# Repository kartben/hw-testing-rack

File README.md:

# hw-testing-rack

**An all-printed, tilted test rack for development boards (12 in its default
4 × 3 layout) — every board in its own sliding drawer, power-switched,
current-metered and exposed over the network with USB/IP by a Zephyr-powered
ESP32-S3 in each bay.**

**[▶ Interactive 3D model](https://kartben.github.io/hw-testing-rack/)** · [Logic analyzer](https://kartben.github.io/hw-testing-rack/analyzer/) · [BOM](bom/README.md) ·
[Architecture](docs/architecture.md) · [Mechanics](docs/mechanical.md) · [Cabling](docs/cabling.md) ·
[Power](docs/power.md) · [Electronics](docs/electronics.md) · [Assembly](docs/assembly.md) ·
[Firmware](docs/firmware.md) · [Standalone bays](docs/standalone.md) · [CI](docs/ci.md)

## Highlights

* **Printed panel frame, no aluminium** — side walls ("ladders") shared by
  neighbouring bays, stacked row on row with snap hooks; trays slide into
  their grooves and click in; a taut X brace behind every bay keeps it square.
  Rows tilt 20° so every board, LED and label faces you, and the grid grows
  in both directions.
* **Drawers that stay connected** — each bay is a drawer sliding 140 mm along
  the slope; a drag chain hidden in the floor carries the cable, so you can
  pull a board out to probe it while it keeps running.
* **One plate for every board** — a honeycomb plate in each drawer; clip-in
  pegs (stops, cams, pins) hold any board on it, placed by a tool from a small
  board library (UNO, Nucleo-64/144, Pico, nRF DKs, FRDM, …): up to four small
  boards on one plate.
* **One ESP32-S3 per bay** — switches the board's 5 V (current-limited,
  default on), measures V/I (INA226), drives UART/RESET/BOOT lines, and
  exports the board's USB with Zephyr's USB/IP host service.  Plug a laptop
  into the bay's front port and the USB data path switches to it — the
  "classic" way still works, even with no firmware.
* **One USB-C charger** — a printed power box under the first column holds
  the hub: a USB PD 3.1 sink (20 or 28 V from one charger, no mains in the
  rack) and an eFuse per row; a 60 V-rated buck in every bay.  The same row
  cables carry a CAN bus for the rack controller ([can.md](docs/can.md)).
* **Cameras** — an optional Arducam Mega (SPI, 145° M12 lens) and white LEDs behind a diffuser hang from a bay's ceiling, driven by the bay's own node.
* **Everything is generated** from [`config/rack.yaml`](config/rack.yaml):
  OpenSCAD parts, KiCad schematics *and* PCBs (schematic-as-code, Freerouting),
  the BOM with LCSC part numbers, and the interactive viewer.

| | |
|---|---|
|  |  |
| Bay B3 pulled out, still connected: a DATA ×4 at the back serves two XIAOs and two Pico 2s | The DATA ×4 up close: a USB-C lead per board, Dupont jumpers wiring a UART between two of them ([real models](docs/boards-3d.md)) |
|  |  |
| Row B: the GIGA's LVGL screen in B2, between two DATA ×4 bays | Bay node — ESP32-S3 (8 MB PSRAM), 2 USB muxes, TPS26600 eFuse, INA226, CAN, 60 V buck |

Neutral technical renders: [the rack](docs/img/hero.jpg), [one bay exploded](docs/architecture.md),
[side view](docs/mechanical.md).

## Repository layout

```
config/rack.yaml          single source of truth (rows, bays, tilt, dimensions, population)
mechanical/               OpenSCAD: lib/, parts/, boards/boards.yaml, generated/ (from the config)
electronics/
  tools/                  schematic-as-code (eda.py), PCB builder (pcbgen.py), catalogue, LCSC resolver
  bay-node/               design.py + generated KiCad project, fab/, docs/
  power-hub/              design.py + generated KiCad project, fab/, docs/
  data-port-x6/           the drawer's DATA ×6, six USB-C, power only (the default): design.py + KiCad, fab/, docs/
  data-port-x4/           the DATA ×4 v2, four USB-C and the logic, for bays with wires: design.py + KiCad, fab/, docs/
  data-port/              the single-port board, retired from the rack, kept for the standalone Solo box
  camera-pod/             the camera pod's board (lead, camera header, 3.3 V, LEDs): design.py + KiCad, fab/, docs/
  lib/                    custom symbol(s), cached JLC basic passives
site/                     GitHub Pages: three.js viewer + BOM page (assets generated)
bom/                      full rack BOM (CSV + summary)
render/                   Blender scene + photoreal renders
tools/                    build.py (config/STL/web), kicad.sh, bom.py, jlc_mcp.py, notice/ (FreeCAD line art)
docs/                     design documentation
```

## Building

Prerequisites: Python ≥ 3.10 with `pyyaml numpy trimesh` (`pip install -r tools/requirements.txt`),
Docker (for KiCad 10, Freerouting and — if not installed locally — OpenSCAD).

```bash
python tools/build.py all                    # config → STLs → web viewer assets
tools/kicad.sh bay-node --route --fab        # schematic, PCB, autoroute, Gerbers/BOM/CPL, renders
tools/kicad.sh power-hub --route --fab
tools/kicad.sh data-port-x6 --fab            # fab outputs of the routed board, no re-route
tools/kicad.sh data-port-x4 --fab
tools/kicad.sh camera-pod --route --fab
python tools/bom.py                          # full rack BOM
python -m http.server -d site 8000           # open http://localhost:8000
```

Generated outputs (STLs, Gerbers, renders, PDFs, GLBs, the BOM) are committed with the change that alters
them, never for a date: `python tools/keep_unchanged.py` puts back every regenerated file whose content didn't
change (`tools/kicad.sh … --fab` runs it on its board).

For screenshots the viewer takes URL parameters: `?bay=B4&openbay=1&view=dut&hideui`
pulls bay B4's drawer out and frames its DUT cable (DATA port to board), with no UI.
`?bay=B2&view=camera&camlight=1&preview=B2` looks into a camera bay with its LEDs on and opens what
its camera sees (an Arducam Mega with a 145° lens: fisheye, noise, auto-exposure and JPEG, at 5 fps).

The viewer lights the rack like the photos: a real room (Poly Haven's "Small Empty Room 1", CC0, cut to
512 × 256 in `site/assets/env/`), AgX with Blender's "Medium High Contrast" look, PETG with its layer lines.
Its *High quality* box (on by default on a desktop GPU, off on phones and small GPUs, and dropped by itself
under 25 fps) adds ambient occlusion (GTAO), a glow on the status LEDs and the camera lights, 4× MSAA through
the post-processing and 4096² sun shadows; `?quality=high` or `?quality=low` forces one for screenshots.

Photoreal renders (Blender + Cycles) start from `render/assembly.glb`, baked
from the same scene as the viewer by `python tools/assembly_glb.py --hq` (`--hq`:
full-resolution part meshes instead of the viewer's lighter ones).  Either
render headless in Docker (`tools/render.sh hero`) or drive a Blender you
already have open — GPU and all — through the Blender MCP add-on's socket:

```bash
python tools/blender_live.py exec render/live_scene.py                    # (re)build the scene
python tools/blender_live.py exec render/live_render.py hero              # → docs/img/hero.jpg
python tools/blender_live.py exec render/live_render.py drawer:B3 docs/img/drawer.jpg

python tools/assembly_glb.py --hq --explode-bay B2 --out render/bay-exploded.glb   # one bay, layers apart
python tools/blender_live.py exec render/live_scene.py render/bay-exploded.glb
python tools/blender_live.py exec render/live_render.py exploded
```

The photo shots (`docs/img/photo-*.jpg`) use their own scene: a small office
lit through a window, PETG with 0.2 mm layer lines and
rounded edges, scanned oak and plaster (CC0 textures from Poly Haven), a laptop
showing a Zephyr shell, wired to bay B4 by a USB-C cable that hangs as a real
one would (a catenary), depth of field, bloom and a vignette, rendered at 2× and averaged down:

```bash
python tools/fetch_render_assets.py                     # CC0 textures + vendor board models → render/assets/
python tools/board_models.py                            # normalise the board models (docs/boards-3d.md)
python render/screen_terminal.py                        # the laptop's screen → render/assets/
node tools/lvgl_frame.mjs music 480 800                 # B2's GIGA display: one frame of the viewer's LVGL demo
                                                        # (the drawer fronts' status screens: assembly_glb.py draws them)
python tools/assembly_glb.py --hq --with-pc-cable --open-bays B3 --out render/assembly-photo.glb
python tools/blender_live.py exec render/live_photo.py build
python tools/blender_live.py exec render/live_photo.py shot desk          # desk, drawer, detail → docs/img/photo-*.jpg
```

Change the rack in `config/rack.yaml` (tilt, rows, columns, panel thickness,
which bays get cameras, which board sits where) and rebuild.

## Status

v0.2 — the printed panel frame replaces the aluminium frame, **not yet
built**.  Mechanics are printable and parametric, the power box included;
still to design: double-width bays (see [mechanical.md](docs/mechanical.md)).
Each drawer front carries the node's 1.9" touch display, waiting on the
module to check its fit before a test print.  Five PCBs (bay node, power hub,
DATA ×6, DATA ×4, camera pod) pass ERC and DRC, are routed and smoothed,
and went through a schematic review
([schematic-review-2026-10-25.md](docs/schematic-review-2026-10-25.md)) and a
datasheet audit.  **Their v1.0 went to fabrication on 2026-11-11** and is
frozen: a change to a board now takes a new revision
([electronics.md › Revisions at the fab](docs/electronics.md#revisions-at-the-fab)).
None is on the bench yet; what to check when they arrive:
[bring-up.md](docs/bring-up.md).  The node firmware:
[firmware.md](docs/firmware.md).
Board outlines marked `verified: false` in `boards.yaml` are approximate.

## License

Hardware (mechanical and electronics design files): **CERN-OHL-P-2.0**.
Software (tools, viewer, firmware): **Apache-2.0**.  See [LICENSE](LICENSE).

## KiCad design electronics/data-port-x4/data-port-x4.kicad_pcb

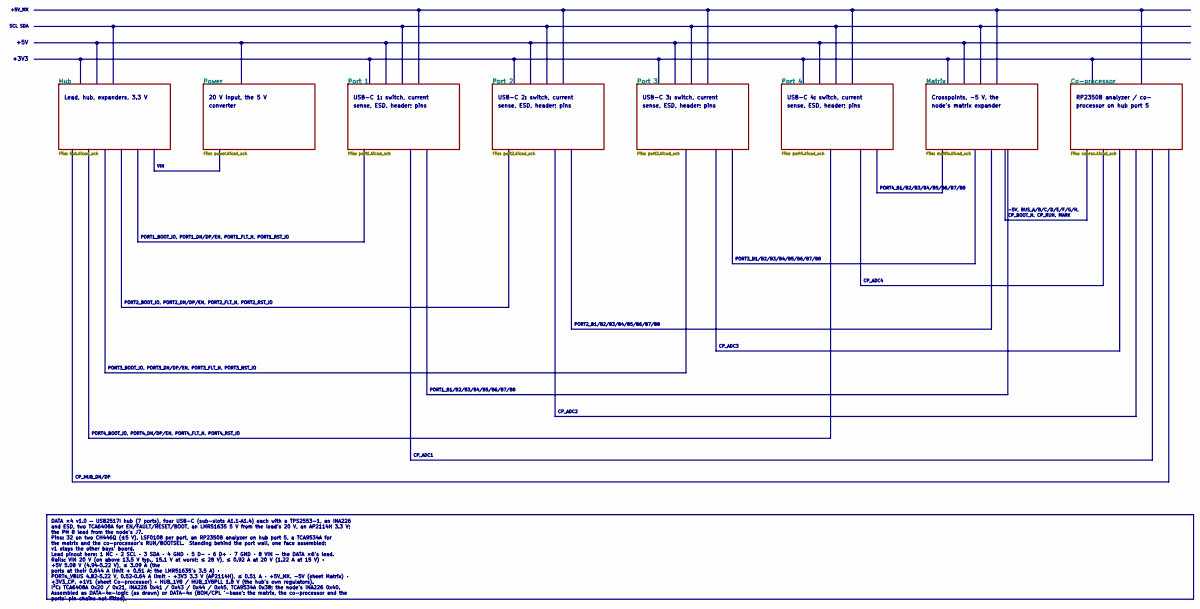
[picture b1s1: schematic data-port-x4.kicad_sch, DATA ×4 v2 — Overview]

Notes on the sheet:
Lead, hub, expanders, 3.3 V
20 V input, the 5 V
converter
USB-C 1: switch, current
sense, ESD, header; pins
USB-C 2: switch, current
USB-C 3: switch, current
USB-C 4: switch, current
Crosspoints, −5 V, the
node's matrix expander
RP2350B analyzer / co-
processor on hub port 5
+3V3
+5V
SCL SDA
+5V_MX
VIN
PORT4_B1/B2/B3/B4/B5/B6/B7/B8
-5V, BUS_A/B/C/D/E/F/G/H,
CP_BOOT_N, CP_RUN, MARK
PORT1_BOOT_IO, PORT1_DN/DP/EN, PORT1_FLT_N, PORT1_RST_IO
PORT3_B1/B2/B3/B4/B5/B6/B7/B8
CP_ADC4
PORT2_BOOT_IO, PORT2_DN/DP/EN, PORT2_FLT_N, PORT2_RST_IO
PORT2_B1/B2/B3/B4/B5/B6/B7/B8
CP_ADC3
PORT3_BOOT_IO, PORT3_DN/DP/EN, PORT3_FLT_N, PORT3_RST_IO
PORT1_B1/B2/B3/B4/B5/B6/B7/B8
CP_ADC2
PORT4_BOOT_IO, PORT4_DN/DP/EN, PORT4_FLT_N, PORT4_RST_IO
CP_ADC1
CP_HUB_DN/DP
DATA ×4 v1.0 — USB2517I hub (7 ports), four USB-C (sub-slots A1.1–A1.4) each with a TPS2553-1, an INA226 and ESD, two TCA6408A for EN/FAULT/RESET/BOOT, an LMR51635 5 V from the lead's 20 V, an AP2114H 3.3 V; the PH 8 lead from the node's J7. Pins: 32 on two CH446Q (±5 V), LSF0108 per port, an RP235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

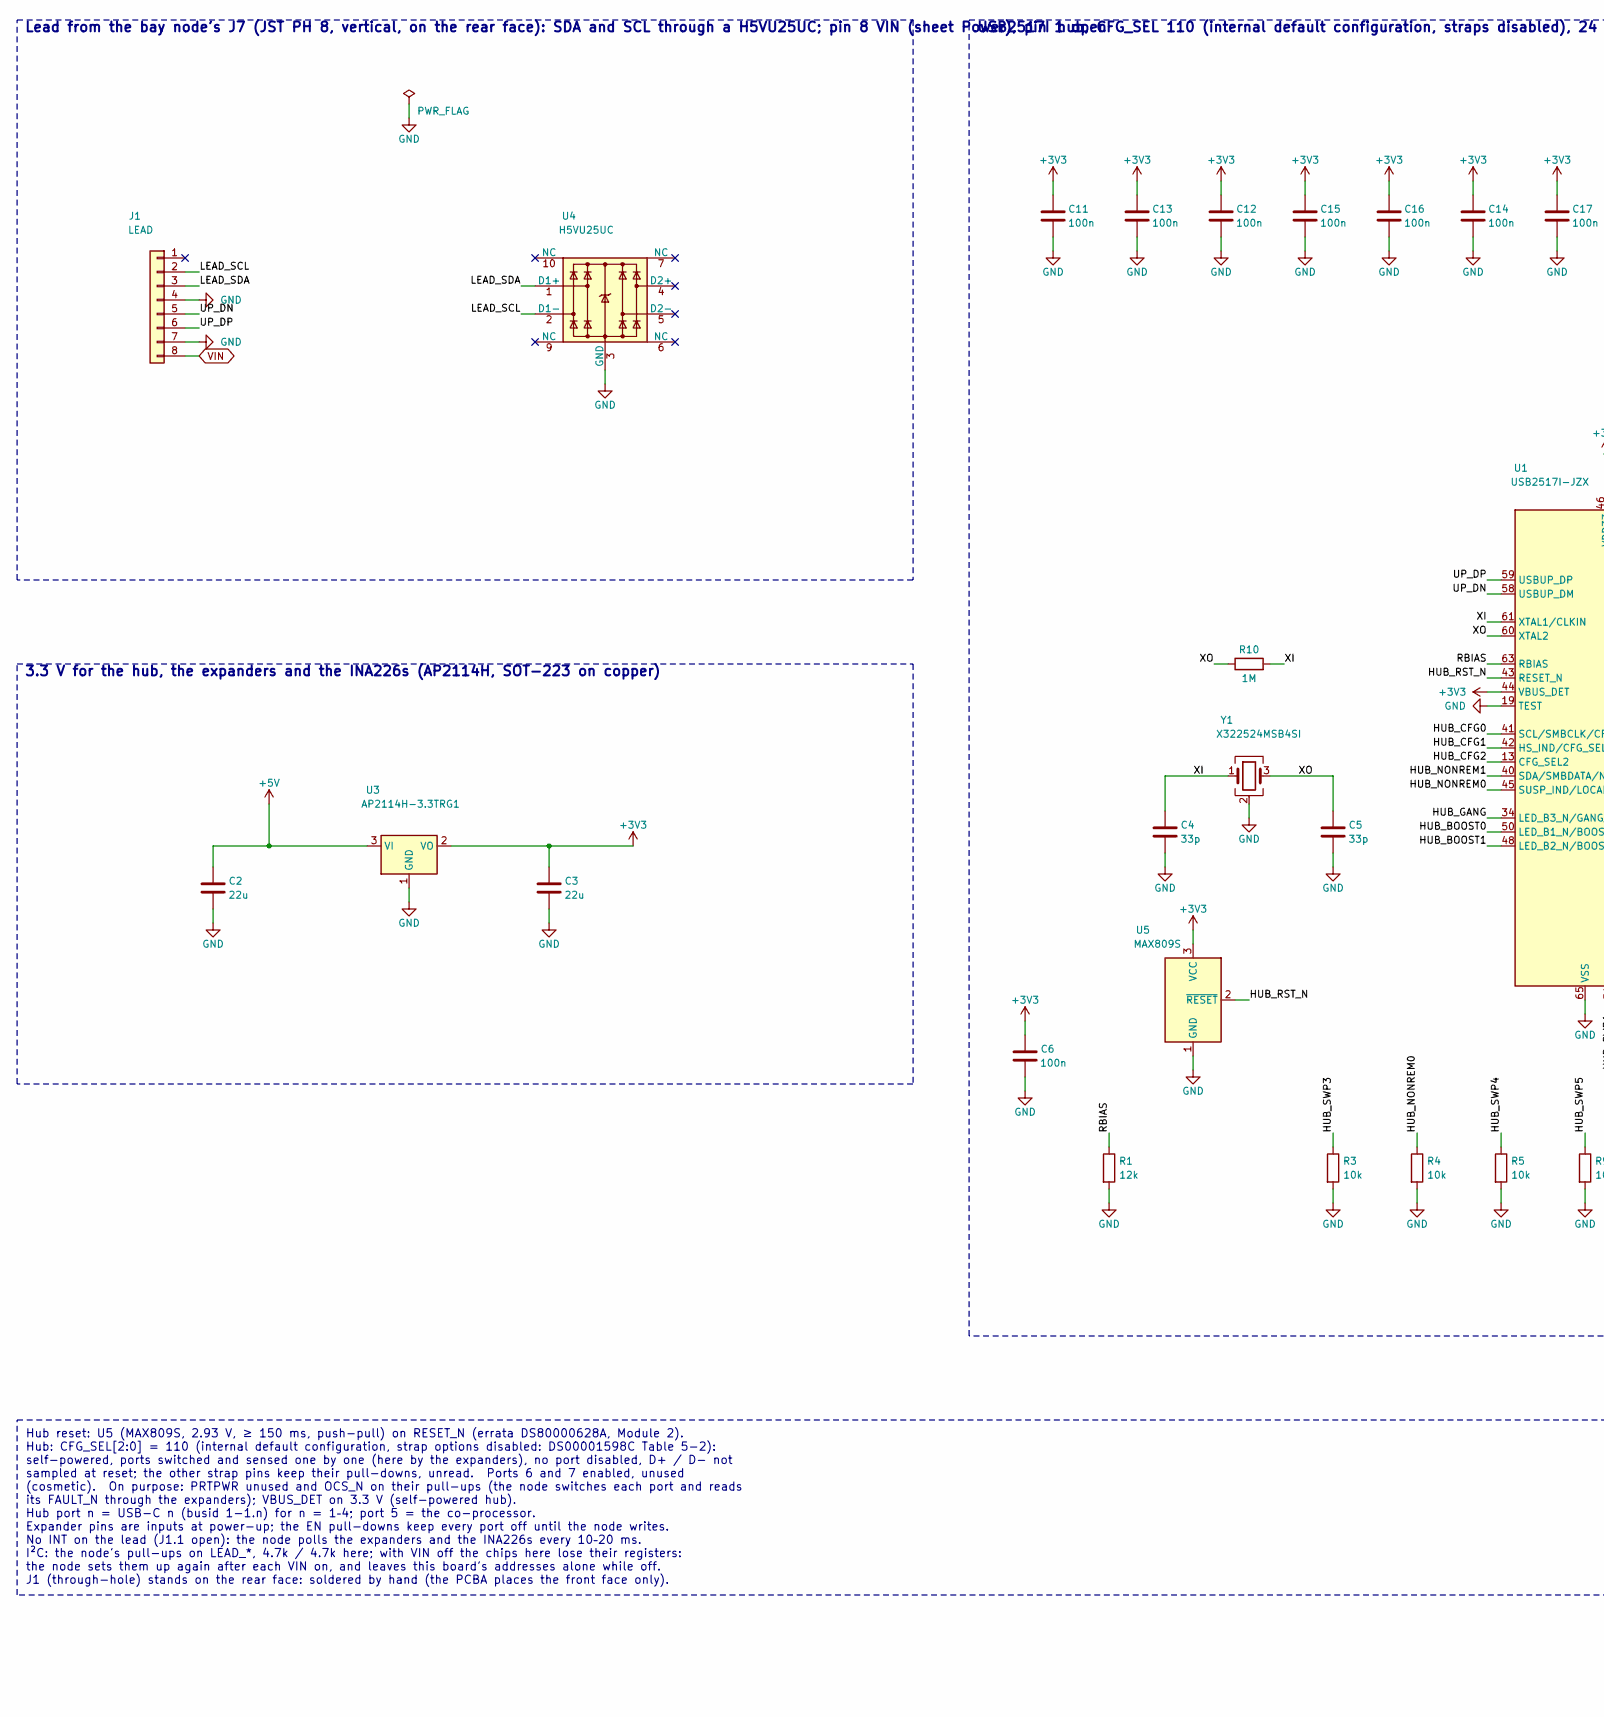
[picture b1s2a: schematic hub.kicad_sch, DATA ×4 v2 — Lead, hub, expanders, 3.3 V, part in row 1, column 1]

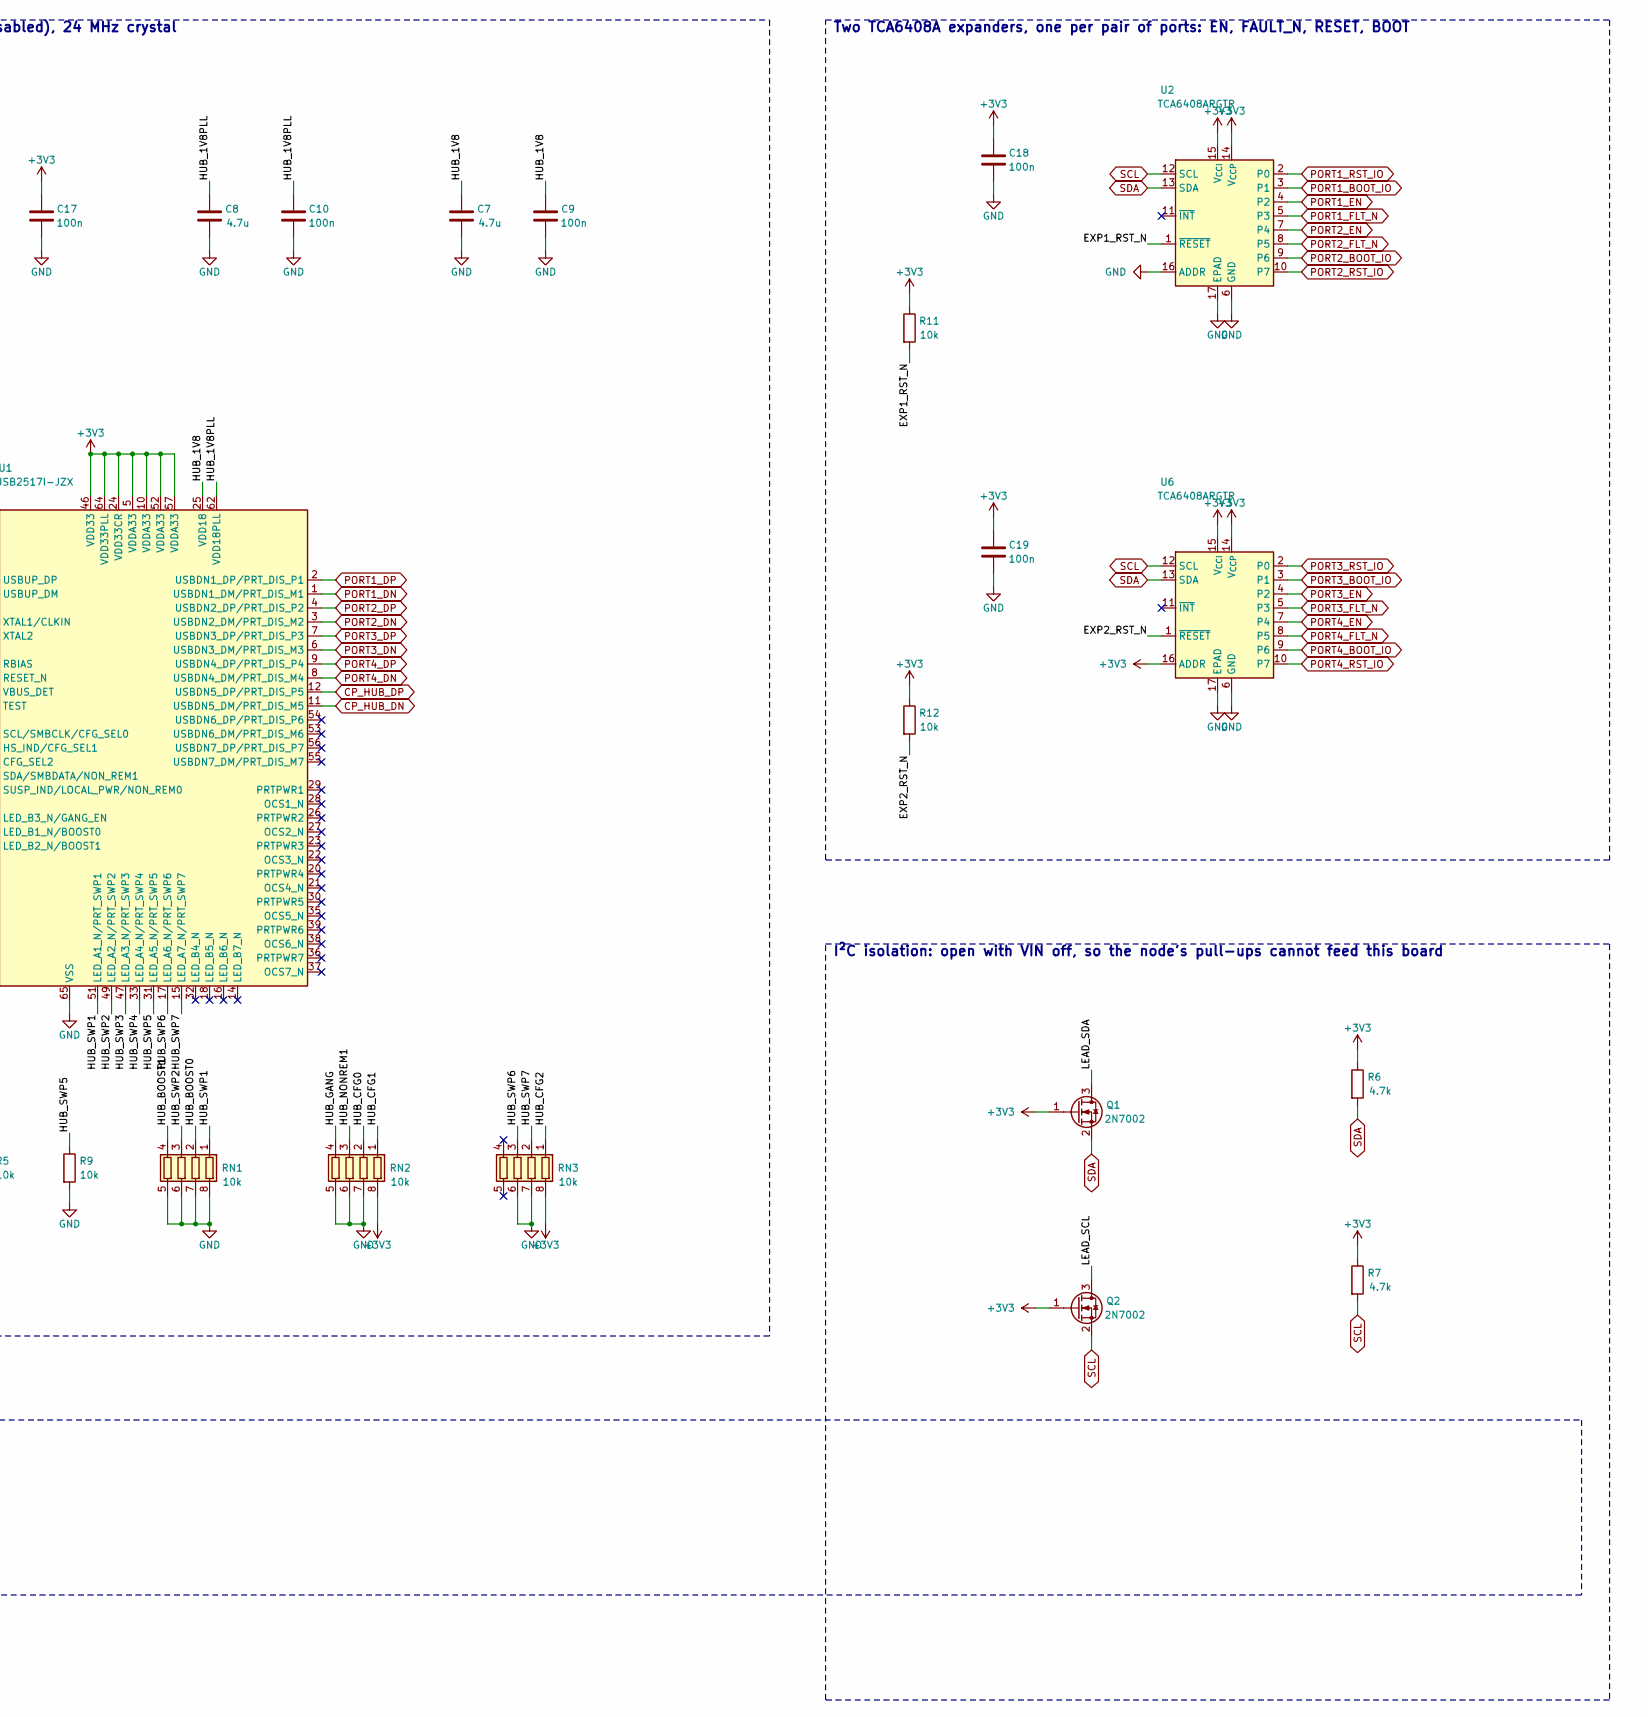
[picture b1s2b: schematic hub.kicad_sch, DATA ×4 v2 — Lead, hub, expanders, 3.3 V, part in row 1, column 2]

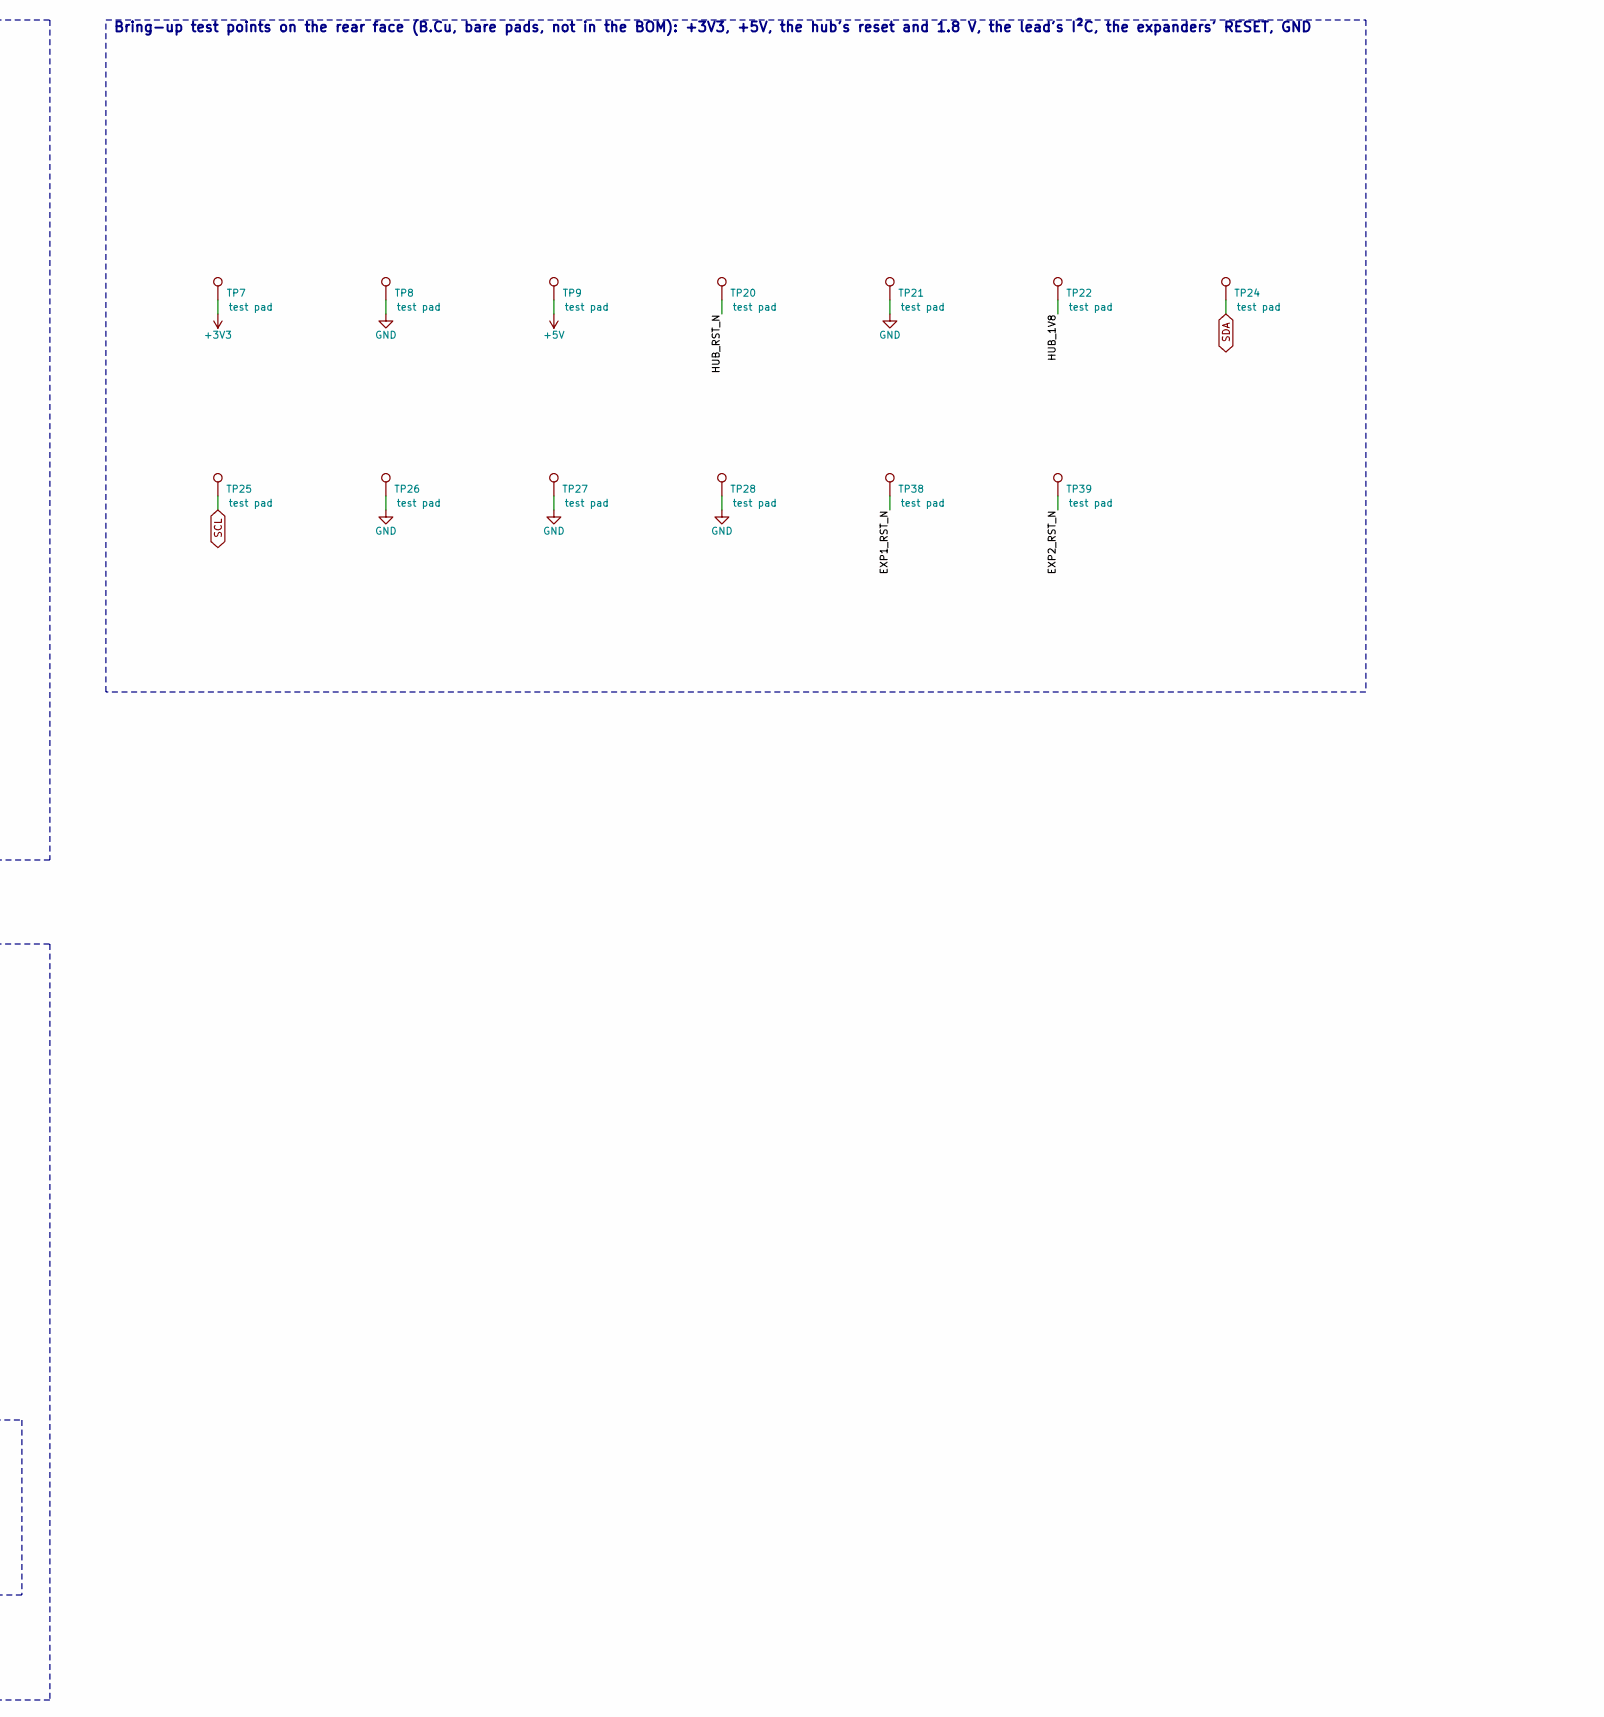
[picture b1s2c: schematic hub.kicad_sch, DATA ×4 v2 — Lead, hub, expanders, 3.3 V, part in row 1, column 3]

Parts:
C2, C3: 22u; C_0805_2012Metric; MPN CL21A226MAQNNNE; LCSC C45783
C4, C5: 33p; C_0402_1005Metric; MPN 0402CG330J500NT; LCSC C1562
C6, C9, C10, C11, C12, C13, C14, C15, C16, C17, C18, C19: 100n; C_0402_1005Metric; MPN CL05B104KO5NNNC; LCSC C1525
C7, C8: 4.7u; C_0402_1005Metric; MPN CL05A475MP5NRNC; LCSC C23733
J1: LEAD; JST_PH_B8B-PH-K_1x08_P2.00mm_Vertical; MPN B8B-PH-K-S(LF)(SN); LCSC C157974
Q1, Q2: 2N7002; SOT-23; MPN 2N7002; LCSC C8545
R1: 12k; R_0402_1005Metric; MPN 0402WGF1202TCE; LCSC C25752
R3, R4, R5, R9, R11, R12: 10k; R_0402_1005Metric; MPN 0402WGF1002TCE; LCSC C25744
R6, R7: 4.7k; R_0402_1005Metric; MPN 0402WGF4701TCE; LCSC C25900
R10: 1M; R_0402_1005Metric; MPN 0402WGF1004TCE; LCSC C26083
RN1, RN2, RN3: 10k; R_Array_Convex_4x0402; MPN 4D02WGJ0103TCE; LCSC C25725
TP7, TP8, TP9, TP21, TP22, TP26, TP27, TP28: test pad; TestPoint_Pad_D1.5mm; MPN test pad
TP20, TP24, TP25, TP38, TP39: test pad; TestPoint_Pad_D1.0mm; MPN test pad
U1: USB2517I-JZX; QFN-64-1EP_9x9mm_P0.5mm_EP4.7x4.7mm_Paste4x4; MPN USB2517I-JZX; LCSC C478081
U2, U6: TCA6408ARGTR; VQFN-16-1EP_3x3mm_P0.5mm_EP1.45x1.45mm; MPN TCA6408ARGTR; LCSC C181499
U3: AP2114H-3.3TRG1; SOT-223-3_TabPin2; MPN AP2114H-3.3TRG1; LCSC C150716
U4: H5VU25UC; DFN2510-10L_2.5x1.0mm_P0.5mm; MPN H5VU25UC; LCSC C20615800
U5: MAX809S; SOT-23; MPN MAX809S; LCSC C347371
Y1: X322524MSB4SI; Crystal_SMD_3225-4Pin_3.2x2.5mm; MPN X322524MSB4SI; LCSC C15643

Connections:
+3V3: C3.1, C6.1, C11.1, C12.1, C13.1, C14.1, C15.1, C16.1, C17.1, C18.1, C19.1, Q1.1 (G), Q2.1 (G), R6.1, R7.1, R11.1, R12.1, RN2.8 (R1.2), RN3.8 (R1.2), TP7.1, U1.5 (VDDA33), U1.10 (VDDA33), U1.24 (VDD33CR), U1.44 (VBUS_DET), U1.46 (VDD33), U1.52 (VDDA33), U1.57 (VDDA33), U1.64 (VDD33PLL), U2.14 (V_{CCP}), U2.15 (V_{CCI}), U3.2 (VO), U5.3 (VCC), U6.14 (V_{CCP}), U6.15 (V_{CCI}), U6.16 (ADDR); also elsewhere on the board
+5V: C2.1, TP9.1, U3.3 (VI); also elsewhere on the board
/Hub/EXP1_RST_N: R11.2, TP38.1, U2.1 (~RESET)
/Hub/EXP2_RST_N: R12.2, TP39.1, U6.1 (~RESET)
/Hub/HUB_1V8: C7.1, C9.1, TP22.1, U1.25 (VDD18)
/Hub/HUB_1V8PLL: C8.1, C10.1, U1.62 (VDD18PLL)
/Hub/HUB_BOOST0: RN1.2 (R2.1), U1.50 (LED_B1_N/BOOST0)
/Hub/HUB_BOOST1: RN1.4 (R4.1), U1.48 (LED_B2_N/BOOST1)
/Hub/HUB_CFG0: RN2.2 (R2.1), U1.41 (SCL/SMBCLK/CFG_SEL0)
/Hub/HUB_CFG1: RN2.1 (R1.1), U1.42 (HS_IND/CFG_SEL1)
/Hub/HUB_CFG2: RN3.1 (R1.1), U1.13 (CFG_SEL2)
/Hub/HUB_GANG: RN2.4 (R4.1), U1.34 (LED_B3_N/GANG_EN)
/Hub/HUB_NONREM0: R4.1, U1.45 (SUSP_IND/LOCAL_PWR/NON_REM0)
/Hub/HUB_NONREM1: RN2.3 (R3.1), U1.40 (SDA/SMBDATA/NON_REM1)
/Hub/HUB_RST_N: TP20.1, U1.43 (RESET_N), U5.2 (~RESET)
/Hub/HUB_SWP1: RN1.1 (R1.1), U1.51 (LED_A1_N/PRT_SWP1)
/Hub/HUB_SWP2: RN1.3 (R3.1), U1.49 (LED_A2_N/PRT_SWP2)
/Hub/HUB_SWP3: R3.1, U1.47 (LED_A3_N/PRT_SWP3)
/Hub/HUB_SWP4: R5.1, U1.33 (LED_A4_N/PRT_SWP4)
/Hub/HUB_SWP5: R9.1, U1.31 (LED_A5_N/PRT_SWP5)
/Hub/HUB_SWP6: RN3.3 (R3.1), U1.17 (LED_A6_N/PRT_SWP6)
/Hub/HUB_SWP7: RN3.2 (R2.1), U1.15 (LED_A7_N/PRT_SWP7)
/Hub/LEAD_SCL: J1.2, Q2.3 (D), U4.2 (D1-)
/Hub/LEAD_SDA: J1.3, Q1.3 (D), U4.1 (D1+)
/Hub/RBIAS: R1.1, U1.63 (RBIAS)
/Hub/UP_DN: J1.5, U1.58 (USBUP_DM)
/Hub/UP_DP: J1.6, U1.59 (USBUP_DP)
/Hub/XI: C4.1, R10.2, U1.61 (XTAL1/CLKIN), Y1.1
/Hub/XO: C5.1, R10.1, U1.60 (XTAL2), Y1.3
CP_HUB_DN: U1.11 (USBDN5_DM/PRT_DIS_M5); also elsewhere on the board
CP_HUB_DP: U1.12 (USBDN5_DP/PRT_DIS_P5); also elsewhere on the board
GND: C2.2, C3.2, C4.2, C5.2, C6.2, C7.2, C8.2, C9.2, C10.2, C11.2, C12.2, C13.2, C14.2, C15.2, C16.2, C17.2, C18.2, C19.2, J1.4, J1.7, R1.2, R3.2, R4.2, R5.2, R9.2, RN1.5 (R4.2), RN1.6 (R3.2), RN1.7 (R2.2), RN1.8 (R1.2), RN2.5 (R4.2), RN2.6 (R3.2), RN2.7 (R2.2), RN3.6 (R3.2), RN3.7 (R2.2), TP8.1, TP21.1, TP26.1, TP27.1, TP28.1, U1.19 (TEST), U1.65 (VSS), U2.6 (GND), U2.16 (ADDR), U2.17 (EPAD), U3.1 (GND), U4.3 (GND), U4.8 (GND), U5.1 (GND), U6.6 (GND), U6.17 (EPAD), Y1.2 (G), Y1.4 (G); also elsewhere on the board
PORT1_BOOT_IO: U2.3 (P1); also elsewhere on the board
PORT1_DN: U1.1 (USBDN1_DM/PRT_DIS_M1); also elsewhere on the board
PORT1_DP: U1.2 (USBDN1_DP/PRT_DIS_P1); also elsewhere on the board
PORT1_EN: U2.4 (P2); also elsewhere on the board
PORT1_FLT_N: U2.5 (P3); also elsewhere on the board
PORT1_RST_IO: U2.2 (P0); also elsewhere on the board
PORT2_BOOT_IO: U2.9 (P6); also elsewhere on the board
PORT2_DN: U1.3 (USBDN2_DM/PRT_DIS_M2); also elsewhere on the board
PORT2_DP: U1.4 (USBDN2_DP/PRT_DIS_P2); also elsewhere on the board
PORT2_EN: U2.7 (P4); also elsewhere on the board
PORT2_FLT_N: U2.8 (P5); also elsewhere on the board
PORT2_RST_IO: U2.10 (P7); also elsewhere on the board
PORT3_BOOT_IO: U6.3 (P1); also elsewhere on the board
PORT3_DN: U1.6 (USBDN3_DM/PRT_DIS_M3); also elsewhere on the board
PORT3_DP: U1.7 (USBDN3_DP/PRT_DIS_P3); also elsewhere on the board
PORT3_EN: U6.4 (P2); also elsewhere on the board
PORT3_FLT_N: U6.5 (P3); also elsewhere on the board
PORT3_RST_IO: U6.2 (P0); also elsewhere on the board
PORT4_BOOT_IO: U6.9 (P6); also elsewhere on the board
PORT4_DN: U1.8 (USBDN4_DM/PRT_DIS_M4); also elsewhere on the board
PORT4_DP: U1.9 (USBDN4_DP/PRT_DIS_P4); also elsewhere on the board
PORT4_EN: U6.7 (P4); also elsewhere on the board
PORT4_FLT_N: U6.8 (P5); also elsewhere on the board
PORT4_RST_IO: U6.10 (P7); also elsewhere on the board
SCL: Q2.2 (S), R7.2, TP25.1, U2.12 (SCL), U6.12 (SCL); also elsewhere on the board
SDA: Q1.2 (S), R6.2, TP24.1, U2.13 (SDA), U6.13 (SDA); also elsewhere on the board
VIN: J1.8; also elsewhere on the board

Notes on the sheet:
Lead from the bay node's J7 (JST PH 8, vertical, on the rear face): SDA and SCL through a H5VU25UC; pin 8 VIN (sheet Power), pin 1 open
3.3 V for the hub, the expanders and the INA226s (AP2114H, SOT-223 on copper)
USB2517I hub, CFG_SEL 110 (internal default configuration, straps disabled), 24 MHz crystal
Two TCA6408A expanders, one per pair of ports: EN, FAULT_N, RESET, BOOT
I²C isolation: open with VIN off, so the node's pull-ups cannot feed this board
Bring-up test points on the rear face (B.Cu, bare pads, not in the BOM): +3V3, +5V, the hub's reset and 1.8 V, the lead's I²C, the expanders' RESET, GND
Hub reset: U5 (MAX809S, 2.93 V, ≥ 150 ms, push-pull) on RESET_N (errata DS80000628A, Module 2). Hub: CFG_SEL[2:0] = 110 (internal default configuration, strap options disabled: DS00001598C Table 5-2): self-powered, ports switched and sensed one by one (here by the expanders), no port disabled, D+ /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

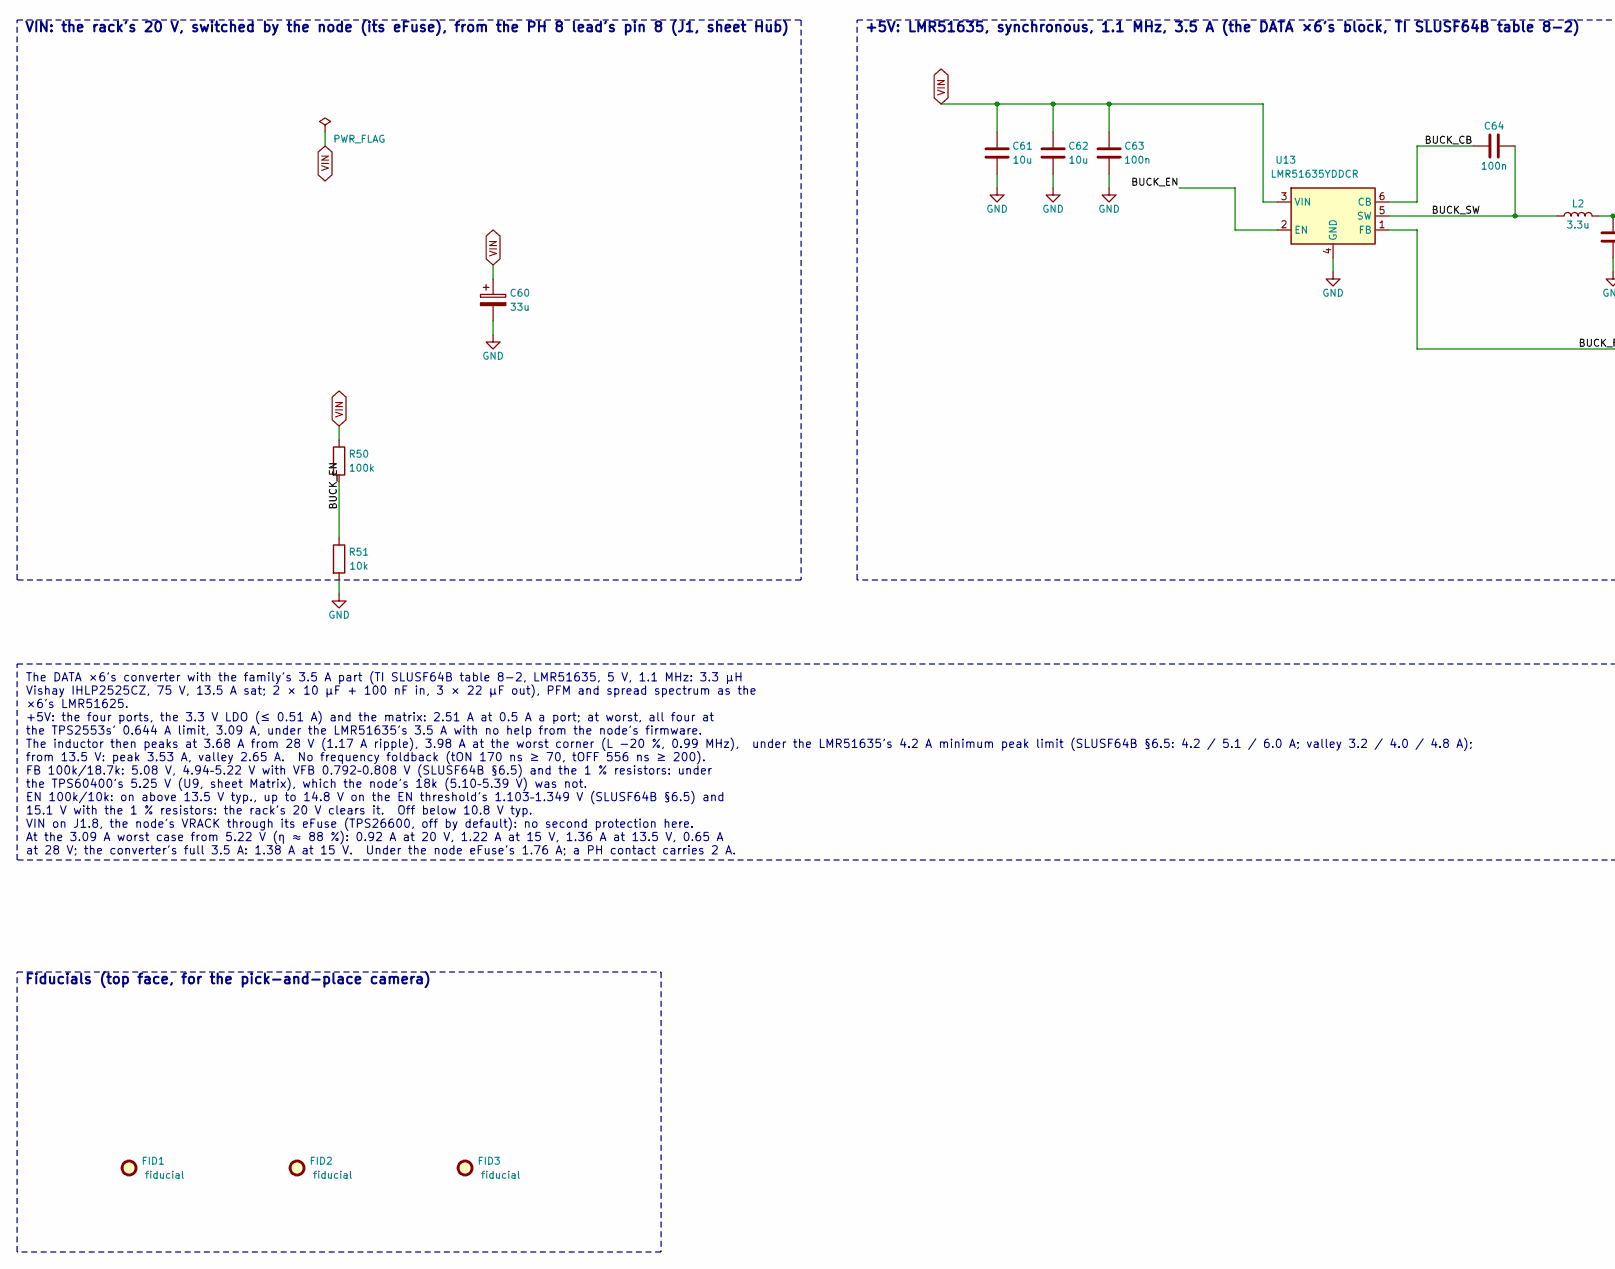
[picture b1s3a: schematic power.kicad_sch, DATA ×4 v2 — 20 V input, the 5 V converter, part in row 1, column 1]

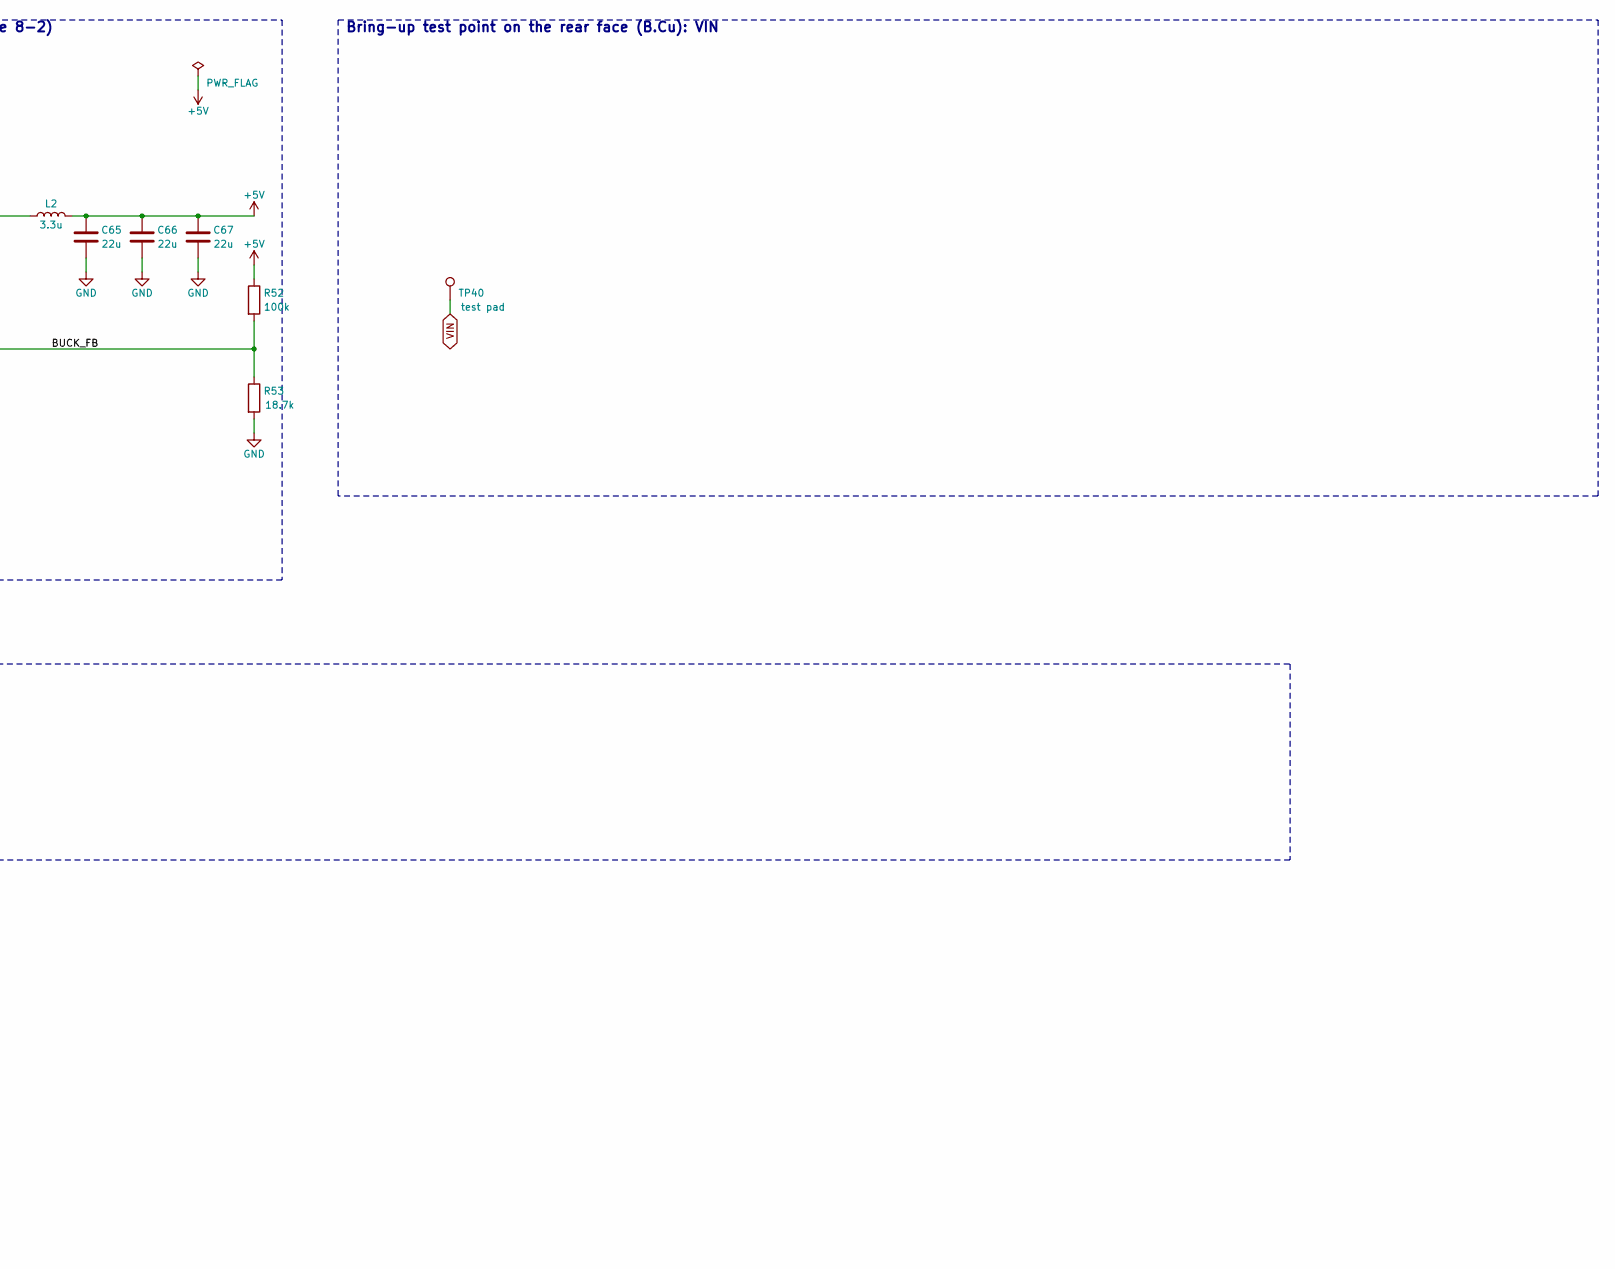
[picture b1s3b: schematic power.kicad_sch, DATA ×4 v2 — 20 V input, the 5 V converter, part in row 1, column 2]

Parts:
C60: 33u; CP_Elec_6.3x7.7; MPN VH1H330ME077000CE0; LCSC C240518
C61, C62: 10u; C_1206_3216Metric; MPN CL31A106KBHNNNE; LCSC C13585
C63, C64: 100n; C_0603_1608Metric; MPN CC0603KRX7R9BB104; LCSC C14663
C65, C66, C67: 22u; C_1206_3216Metric; MPN CL31A226KAHNNNE; LCSC C12891
FID1, FID2, FID3: fiducial; Fiducial_1mm_Mask2mm; MPN fiducial
L2: 3.3u; L_Changjiang_FXL0630; MPN IHLP2525CZER3R3M01; LCSC C506574
R50: 100k; R_0402_1005Metric; MPN 0402WGF1003TCE; LCSC C25741
R51: 10k; R_0402_1005Metric; MPN 0402WGF1002TCE; LCSC C25744
R52: 100k; R_0603_1608Metric; MPN 0603WAF1003T5E; LCSC C25803
R53: 18.7k; R_0603_1608Metric; MPN 0603WAF1872T5E; LCSC C22893
TP40: test pad; TestPoint_Pad_D1.5mm; MPN test pad
U13: LMR51635YDDCR; TSOT-23-6; MPN LMR51635YDDCR; LCSC C45262770

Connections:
+5V: C65.1, C66.1, C67.1, L2.2, R52.1; also elsewhere on the board
/Power/BUCK_CB: C64.1, U13.6 (CB)
/Power/BUCK_EN: R50.2, R51.1, U13.2 (EN)
/Power/BUCK_FB: R52.2, R53.1, U13.1 (FB)
/Power/BUCK_SW: C64.2, L2.1, U13.5 (SW)
GND: C60.2, C61.2, C62.2, C63.2, C65.2, C66.2, C67.2, R51.2, R53.2, U13.4 (GND); also elsewhere on the board
VIN: C60.1, C61.1, C62.1, C63.1, R50.1, TP40.1, U13.3 (VIN); also elsewhere on the board

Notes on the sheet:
VIN: the rack's 20 V, switched by the node (its eFuse), from the PH 8 lead's pin 8 (J1, sheet Hub)
+5V: LMR51635, synchronous, 1.1 MHz, 3.5 A (the DATA ×6's block, TI SLUSF64B table 8-2)
Bring-up test point on the rear face (B.Cu): VIN
Fiducials (top face, for the pick-and-place camera)
The DATA ×6's converter with the family's 3.5 A part (TI SLUSF64B table 8-2, LMR51635, 5 V, 1.1 MHz: 3.3 µH Vishay IHLP2525CZ, 75 V, 13.5 A sat; 2 × 10 µF + 100 nF in, 3 × 22 µF out), PFM and spread spectrum as the ×6's LMR51625. +5V: the four ports, the 3.3 V LDO (≤ 0.51 A) and the matrix: 2.51 A 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
